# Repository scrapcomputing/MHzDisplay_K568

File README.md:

# Reproduction MHz Display K-568

A reproduction of the K-568 MHz display that was common in 386/486 PC cases.
It is powered by 5V DC (pins +5V, G).
It can display a Turbo and a non-Turbo number, depending on the state of the Turbo switch (pins L C H, Low Common High).
It also drives the Turbo LED accordingly (pins T- and T+).
It can also drive the power LED (pins P- and P+).

# How to configure

# Other MHz display reproductions

- [TD-37S](https://github.com/scrapcomputing/MHzDisplayBlaster)

(please let me know of others you may know)

# Resources

- The best resource for MHz displays: [minuszerodegrees.net](https://www.minuszerodegrees.net/led_speed_display/led_speed_display.htm). It includes photos and manuals for a large selection of displays.

# Bill of materials

Gerber files are published in the [releases](https://github.com/scrapcomputing/MHzDisplay_K568/releases).

Reference      | Quantity| Value    | Footprint/Comments
---------------|---------|----------|----------
N/A            | 1       | 18-DIP LED Display | (e.g., LTD-6440G) 18-DIP (0.600", 15.24mm distance between top and bottom row pins) 2-Digit 7-Segment Display Common Cathode 0.56" Green. Should also work with "188" displays, but I can't find a part number (please let me know if you do). Common anode should also work as long as the pinout is the same, but the power needs to be reversed (i.e., +5 to ground and vice versa).
N/A            | 2       | Conn_02x15      | Connector Male PinHeader 2x15 P2.54mm Vertical
N/A            | 1       | Conn_01x09      | Connector Male PinHeader 1x09 P2.54mm Vertical
R1             | 1       | Resistor 100 Ohms 1/4W | 100 Ohms may be quite dimm, depending on the LED technology of the display, so you may try lower values but these should be 1/2W resistors.
N/A            | 15      | Jumpers         | 2.54mm pitch jumpers

# Changelist
- Rev 0.1 : Initial revision

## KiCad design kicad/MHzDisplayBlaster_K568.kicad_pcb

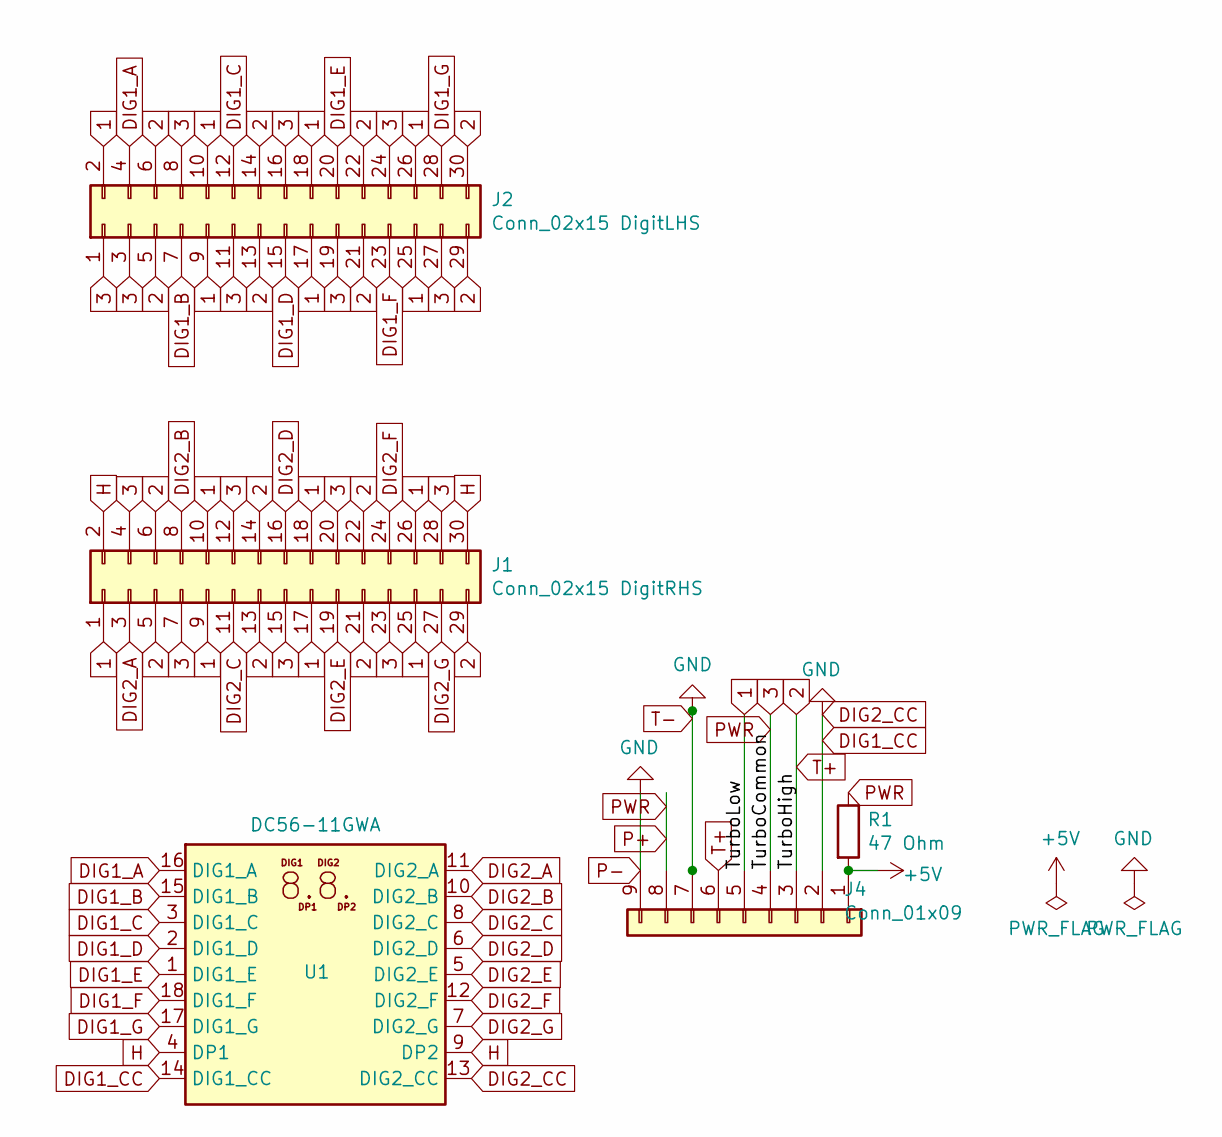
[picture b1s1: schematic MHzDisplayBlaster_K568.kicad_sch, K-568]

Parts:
J1: Conn_02x15 DigitRHS; PinHeader_2x15_P2.54mm_Vertical
J2: Conn_02x15 DigitLHS; PinHeader_2x15_P2.54mm_Vertical
J4: Conn_01x09; PinHeader_1x09_P2.54mm_Vertical
R1: 47 Ohm; R_Axial_DIN0207_L6.3mm_D2.5mm_P10.16mm_Horizontal
U1: DC56-11GWA; DA56-11CGKWA

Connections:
1: J1.1, J1.9, J1.10, J1.17, J1.18, J1.25, J1.26, J2.2, J2.9, J2.10, J2.17, J2.18, J2.25, J2.26, J4.5
2: J1.5, J1.6, J1.13, J1.14, J1.21, J1.22, J1.29, J2.5, J2.6, J2.13, J2.14, J2.21, J2.22, J2.29, J2.30, J4.3, J4.6
3: J1.4, J1.7, J1.12, J1.15, J1.20, J1.23, J1.28, J2.1, J2.3, J2.8, J2.11, J2.16, J2.19, J2.24, J2.27, J4.4, J4.8, R1.1
+5V: J4.1, R1.2
DIG1_A: J2.4, U1.16 (DIG1_A)
DIG1_B: J2.7, U1.15 (DIG1_B)
DIG1_C: J2.12, U1.3 (DIG1_C)
DIG1_CC: J4.2, J4.7, J4.9, U1.13 (DIG2_CC), U1.14 (DIG1_CC)
DIG1_D: J2.15, U1.2 (DIG1_D)
DIG1_E: J2.20, U1.1 (DIG1_E)
DIG1_F: J2.23, U1.18 (DIG1_F)
DIG1_G: J2.28, U1.17 (DIG1_G)
DIG2_A: J1.3, U1.11 (DIG2_A)
DIG2_B: J1.8, U1.10 (DIG2_B)
DIG2_C: J1.11, U1.8 (DIG2_C)
DIG2_D: J1.16, U1.6 (DIG2_D)
DIG2_E: J1.19, U1.5 (DIG2_E)
DIG2_F: J1.24, U1.12 (DIG2_F)
DIG2_G: J1.27, U1.7 (DIG2_G)
H: J1.2, J1.30, U1.4 (DP1), U1.9 (DP2)

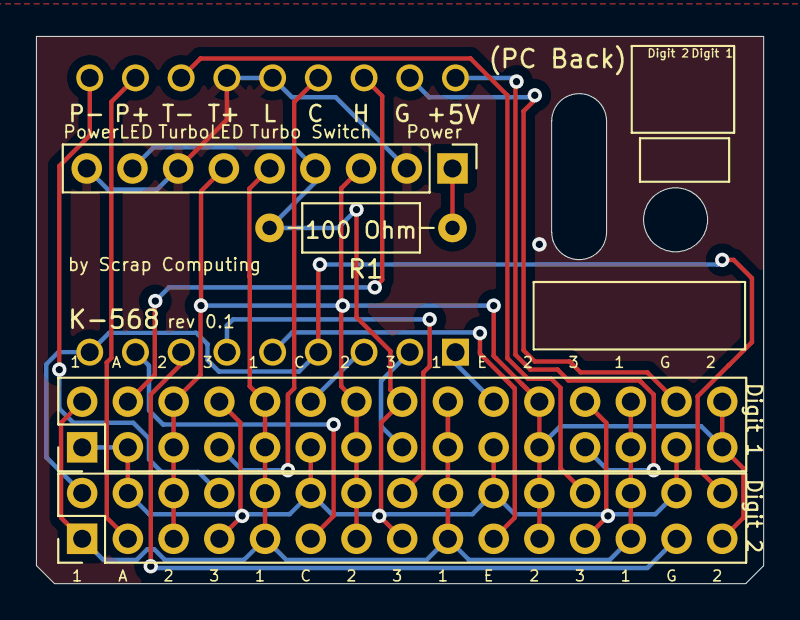
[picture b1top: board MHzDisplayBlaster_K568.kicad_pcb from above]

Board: 2 copper layers, 40.4 x 30.4 mm, 5 parts (1 on the bottom side), 20 nets.

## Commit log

2025-04-18 Rev 0.1
